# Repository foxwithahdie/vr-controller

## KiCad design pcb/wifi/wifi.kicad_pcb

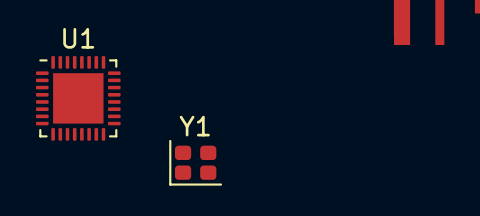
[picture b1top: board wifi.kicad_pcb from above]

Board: 2 copper layers, 3 parts (0 on the bottom side), 3 nets, no tracks yet.

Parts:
A1: ANT_MIFA_TI_AN043
U1: ESP32-H2; QFN-32-1EP_4x4mm_P0.4mm_EP2.9x2.9mm
Y1: Crystal_GND24; Crystal_SMD_2016-4Pin_2.0x1.6mm

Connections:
+3V3: U1.1 (VDD3P3), U1.2 (VDD3P3), U1.9 (VDDPST1), U1.19 (VDDA_PMU), U1.20 (VDDPST2), U1.27 (VDD3P3), U1.30 (VDD3P3), U1.31 (VDD3P3)
/XTAL_N: U1.28 (XTAL_N), Y1.3
GND: U1.33 (GND), Y1.2 (G), Y1.4 (G)
